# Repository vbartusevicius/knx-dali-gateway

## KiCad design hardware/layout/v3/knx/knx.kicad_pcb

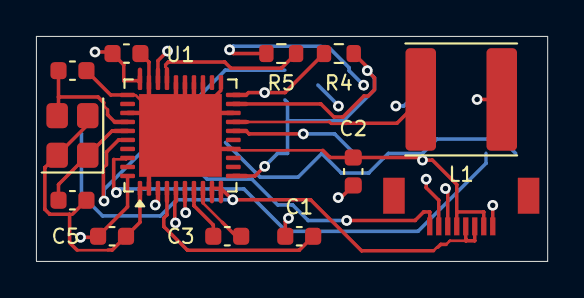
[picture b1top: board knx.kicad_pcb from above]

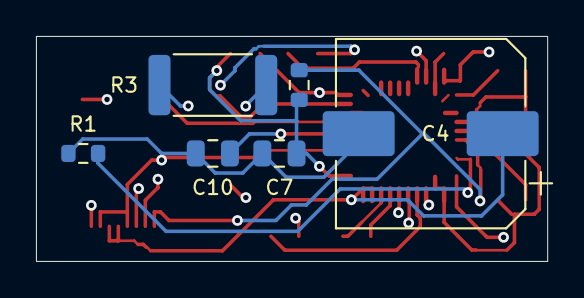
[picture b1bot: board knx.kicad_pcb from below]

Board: 4 copper layers, 28.4 x 12.5 mm, 19 parts (6 on the bottom side), 18 nets.

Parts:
C1: 47n 50V; C_0603_1608Metric
C2, C5, C6: 100n 50V; C_0603_1608Metric
C3: 220n 50V; C_0603_1608Metric
C4: 470u 35V; CP_Elec_10x10
C7: 22u 25V; C_0805_2012Metric
C8, C9: 18p C0G 50V; C_0603_1608Metric
C10: 1u 50V; C_0805_2012Metric
J1: Carrier; FPC_Kinghelm_KH-FPC0.5-H1.2SMT-8P
L1: 220uH; L_Sunlord_SWPA6045S
R1: 10k 1%; R_0603_1608Metric
R2: 10k; R_0603_1608Metric
R3: 27R; R_2512_6332Metric
R4: 1R; R_0603_1608Metric
R5: 1k; R_0603_1608Metric
U1: NCN5130MNTWG; QFN-40-1EP_6x6mm_P0.5mm_EP4.6x4.6mm
Y1: 16MHz; Crystal_SMD_3225-4Pin_3.2x2.5mm

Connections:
+3V3_TRX: C5.1, C6.1, C7.1, R2.1, R4.2, U1.11, U1.19, U1.30, U1.40
CAV: C2.1, U1.5
CCP: C1.2, U1.4
CEQ1: C3.1, U1.7
CEQ2: C3.2, U1.8
FANIN: R1.1, U1.38
GND: C2.2, C4.2, C5.2, C6.2, C7.2, C8.2, C9.2, C10.2, J1.2, J1.5, R1.2, U1.1, U1.2, U1.14, U1.18, U1.21, U1.23, U1.24, U1.25, U1.26, U1.29, U1.31, U1.33, U1.41, Y1.2, Y1.4
KNX_P_PROT: C1.1, J1.1, R3.1, U1.6
KNX_RXD: J1.7, R5.1
KNX_TXD: J1.6, U1.28
unnamed: R5.2, U1.27
NCN_SAVEB: J1.8, R2.2, U1.36
TX0: R3.2, U1.3
VDD1M: L1.2, R4.1, U1.20
VFILT: C4.1, C10.1, J1.3, J1.4, U1.9, U1.10, U1.16
VSW1: L1.1, U1.17
XTAL1: C8.1, U1.35, Y1.1
XTAL2: C9.1, U1.34, Y1.3

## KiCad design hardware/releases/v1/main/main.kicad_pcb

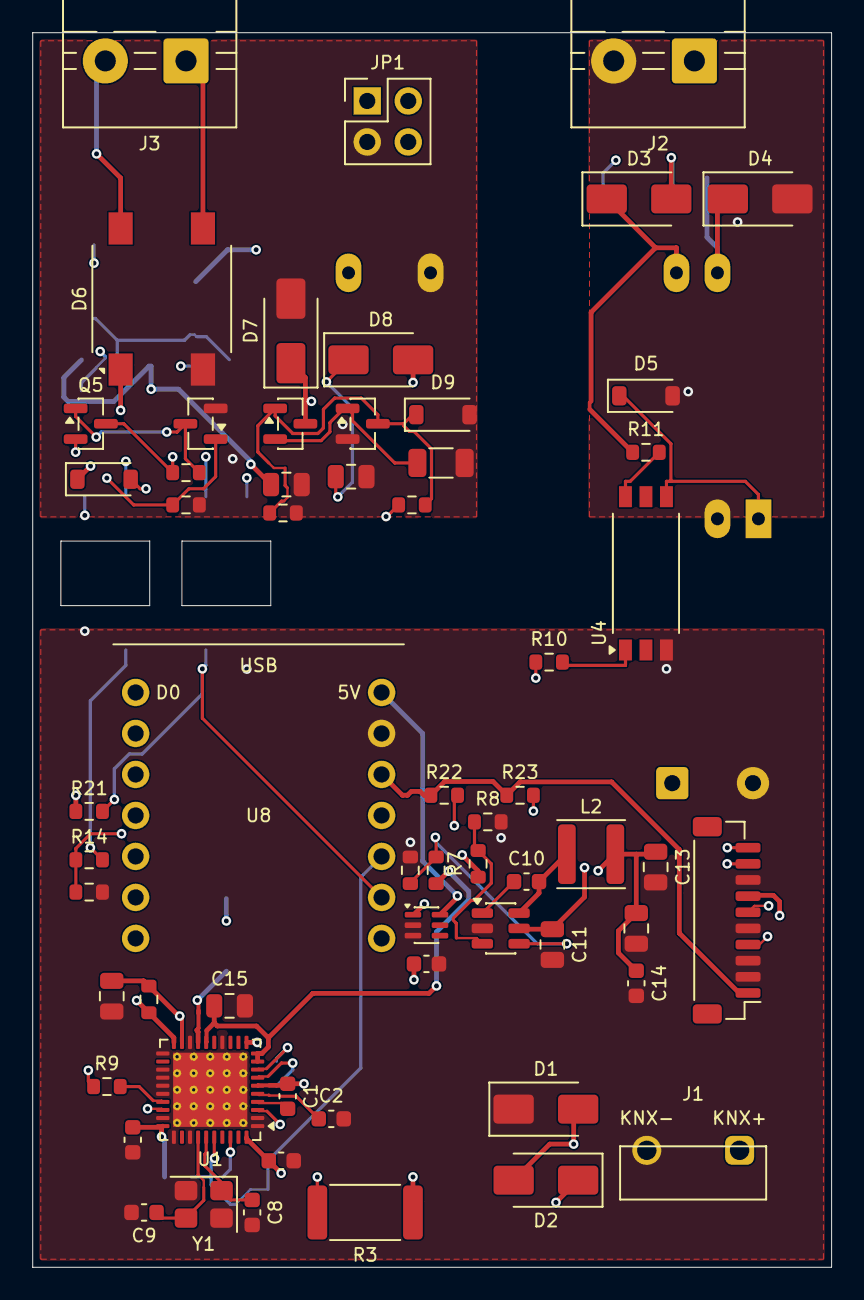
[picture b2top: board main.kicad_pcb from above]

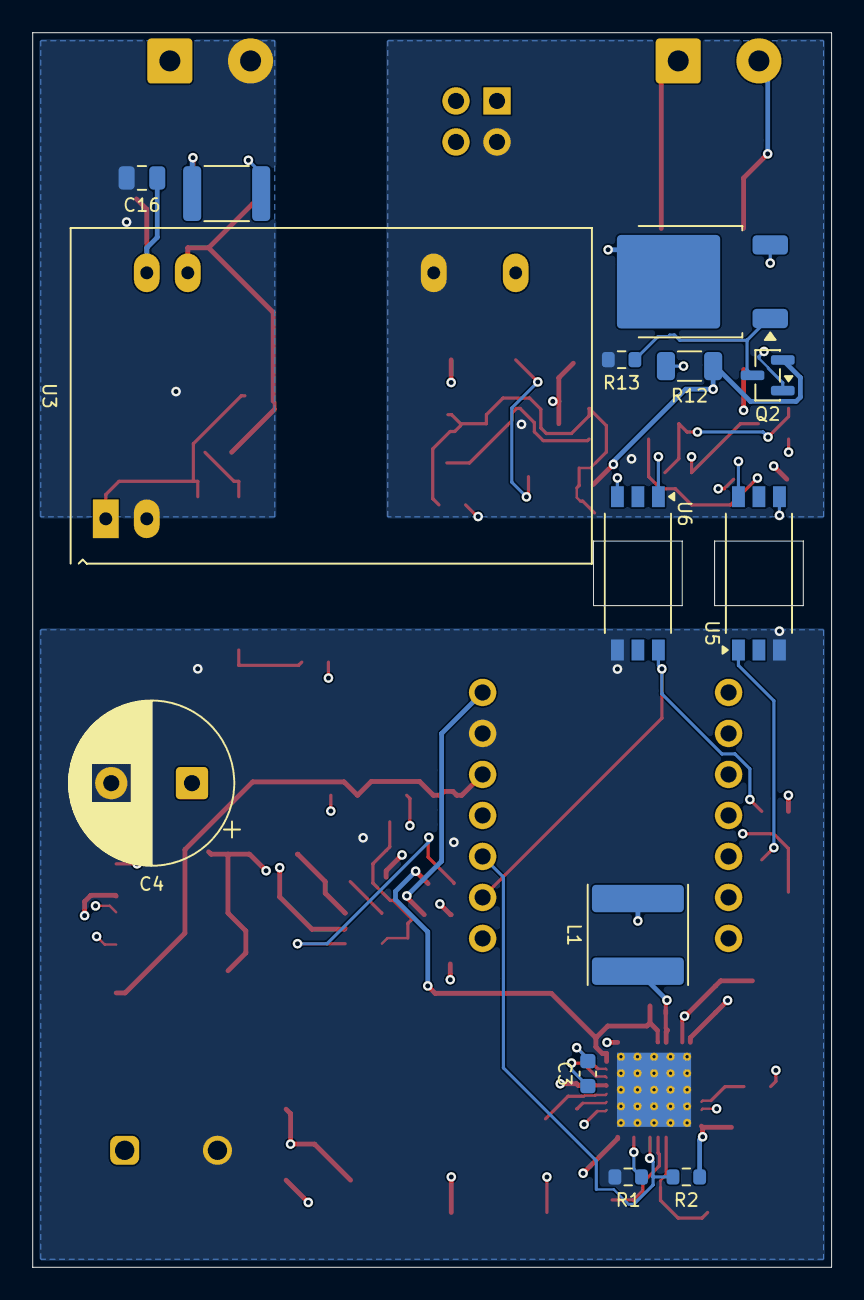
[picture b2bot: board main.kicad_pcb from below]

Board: 4 copper layers, 49.5 x 76.5 mm, 75 parts (14 on the bottom side), 57 nets.

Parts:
C1: 47n 50V; C_0603_1608Metric
C2, C5, C6, C10, C14: 100n 50V; C_0603_1608Metric
C3: 220n 50V; C_0603_1608Metric
C4: 470u 35V; CP_Radial_D10.0mm_P5.00mm
C7, C12, C13: 22u 25V; C_0805_2012Metric
C8, C9: 18p C0G 50V; C_0603_1608Metric
C11, C16: 10u 50V; C_0805_2012Metric
C15, C18: 1u 50V; C_0805_2012Metric
C17: 10u 25V; C_0805_2012Metric
C19: 10u 10V; C_0603_1608Metric
D1: SMAJ40CA; D_SMA
D2, D3, D8: SS16; D_SMA
D4: SMAJ33A; D_SMA
D5, D10: 5V6; D_SOD-123
D6: DF06S; Diode_Bridge_Vishay_DFS
D7: SMAJ24A; D_SMA
D9: 12V; D_SOD-123
F1: 1.1A; Fuse_1812_4532Metric
J1: KNX bus terminal pins; Phoenix_PST_1,0-2-5,75_R32_1x02_P5.75mm
J2: AUX; TerminalBlock_MaiXu_MX126-5.0-02P_1x02_P5.00mm
J3: DALI; TerminalBlock_MaiXu_MX126-5.0-02P_1x02_P5.00mm
J4: JST-SH 1x10; JST_SH_BM10B-SRSS-TB_1x10-1MP_P1.00mm_Vertical
JP1: DALI supply; PinHeader_2x02_P2.54mm_Vertical
L1: 220uH; L_Sunlord_SWPA6045S
L2: 4.7uH; L_APV_ANR4012
Q1: MJD45H11; TO-252-2
Q2: BC857; SOT-23
Q3: IRLML0060; SOT-23
Q4, Q5, Q6: BC847; SOT-23
R1, R6, R8: 10k 1%; R_0603_1608Metric
R2, R11, R15, R21: 10k; R_0603_1608Metric
R3: 27R; R_2512_6332Metric
R4: 1R; R_0603_1608Metric
R5: 120k 1%; R_0603_1608Metric
R7: 51k 1%; R_0603_1608Metric
R9: 1k; R_0603_1608Metric
R10, R14: 330R; R_0603_1608Metric
R12, R18: 3R3; R_1206_3216Metric
R13, R22, R23: 4k7; R_0603_1608Metric
R16: 22k; R_0603_1608Metric
R17, R19: 100k; R_0603_1608Metric
R20: 680R; R_0603_1608Metric
U1: NCN5130MNTWG; QFN-40-1EP_6x6mm_P0.5mm_EP4.6x4.6mm_ThermalVias
U2: SCT2400TVBR; TSOT-23-6
U3: REC3-2415SRW/H2/A/CTRL 24V->15V 3W iso; Converter_DCDC_RECOM_REM3_DIP24_CTRL
U4: TLP383; SO-6L_10x3.84mm_P1.27mm
U5, U6: TLP383(D4BLLTL,E; SO-6L_10x3.84mm_P1.27mm
U7: LM66100; SOT-363_SC-70-6
U8: XIAO ESP32C6; XIAO_ESP32C6_Header
Y1: 16MHz; Crystal_SMD_3225-4Pin_3.2x2.5mm

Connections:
+3V3: J4.1, R21.1, R22.1, R23.1, U8.12
+3V3_TRX: C5.1, C6.1, C7.1, R2.1, R4.2, U1.11, U1.19, U1.30, U1.40
+5V: C12.1, C13.1, C14.1, J4.7, L2.2, R7.1, U7.1
+5V_XIAO: C19.1, U7.6, U8.14
AUX_FUSED: D3.2, F1.2
AUX_P: C16.1, D3.1, D4.1, R11.1, U3.22, U3.23
BTN_LADDER: J4.4, U8.3
CAV: C2.1, U1.5
CCP: C1.2, U1.4
CEQ1: C3.1, U1.7
CEQ2: C3.2, U1.8
DA1: D6.3, J3.1, JP1.2
DA2: D6.4, J3.2, JP1.4
DALI_BOOT: C18.1, D8.1, U5.6
DALI_GATE: D9.1, Q3.1, Q4.3, R16.2, R17.1
DALI_GATE_SW: R16.1, U5.4
DALI_ISO15V: C17.1, Q2.2, R12.1, U3.14
DALI_RX: R21.2, U6.6, U8.9
DALI_SENSE: Q3.2, Q4.1, R18.1
DALI_SUPPLY_OFF: R10.1, U8.2
DALI_SUPPLY_SW: JP1.1, Q1.2
DALI_TX: R14.1, R15.1, U8.11
DA_P: D6.1, D7.1, D8.2, D10.1, Q3.3
FANIN: R1.1, U1.38
GND: C2.2, C4.2, C5.2, C6.2, C7.2, C8.2, C9.2, C11.2, C12.2, C13.2, C14.2, C15.2, C19.2, D1.1, J1.2, J4.2, J4.3, J4.5, J4.8, R1.2, R6.2, R8.2, R15.2, U1.1, U1.2, U1.14, U1.18, U1.21, U1.23, U1.24, U1.25, U1.26, U1.29, U1.31, U1.33, U1.41, U2.2, U4.3, U5.3, U6.4, U7.2, U7.3, U8.13, Y1.2, Y1.4
GNDA: C16.2, D4.2, D5.2, J2.2, U3.2
GNDD: C17.2, C18.2, D6.2, D7.2, D9.2, JP1.3, Q4.2, Q6.2, R13.2, R17.2, R18.2, R20.2, U3.16
I2C_SCL: J4.10, R23.2, U8.6
I2C_SDA: J4.9, R22.2, U8.5
KNX_P: D1.2, D2.2, J1.1
KNX_P_PROT: C1.1, D2.1, R3.1, U1.6
KNX_RXD: R9.1, U8.7
KNX_TXD: U1.28, U8.8
LED_DATA: J4.6, U8.1
unnamed: R5.2, R6.1, U2.4
unnamed: C10.1, U2.1
unnamed: R7.2, R8.1, U2.3
unnamed: R9.2, U1.27
unnamed: F1.1, J2.1
unnamed: R10.2, U4.1
unnamed: R11.2, U4.6
unnamed: D5.1, U3.1, U4.4
unnamed: Q1.3, Q2.1, R12.2
unnamed: Q1.1, Q2.3, R13.1
unnamed: R14.2, U5.1
unnamed: D10.2, U6.1
unnamed: Q5.2, Q6.1, R20.1
unnamed: Q5.1, Q6.3, R19.2
NCN_SAVEB: R2.2, U1.36, U8.10
RX_LIM_IN: Q5.3, R19.1, U6.3
SW: C10.2, L2.1, U2.6
TX0: R3.2, U1.3
VDD1M: L1.2, R4.1, U1.20
VFILT: C4.1, C11.1, C15.1, R5.1, U1.9, U1.10, U1.16, U2.5
VSW1: L1.1, U1.17
XTAL1: C8.1, U1.35, Y1.1
XTAL2: C9.1, U1.34, Y1.3

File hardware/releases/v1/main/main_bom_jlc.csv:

Comment,Designator,Footprint,LCSC Part #
1.1A,F1,Fuse_1812_4532Metric,C142747
100k,"R17,R19",R_0603_1608Metric,C25803
100n 50V,"C10,C14,C2,C5,C6",C_0603_1608Metric,C14663
10k,"R11,R15,R2,R21",R_0603_1608Metric,C25804
10k 1%,"R1,R6,R8",R_0603_1608Metric,C25804
10u 10V,C19,C_0603_1608Metric,C19702
10u 25V,C17,C_0805_2012Metric,C15850
10u 50V,"C11,C16",C_0805_2012Metric,C440198
120k 1%,R5,R_0603_1608Metric,C25808
12V,D9,D_SOD-123,C72599
16MHz,Y1,Crystal_SMD_3225-4Pin_3.2x2.5mm,C12668
18p C0G 50V,"C8,C9",C_0603_1608Metric,C1647
1R,R4,R_0603_1608Metric,C22936
1k,R9,R_0603_1608Metric,C21190
1u 50V,"C15,C18",C_0805_2012Metric,C28323
220n 50V,C3,C_0603_1608Metric,C64705
220uH,L1,L_Sunlord_SWPA6045S,C91047
22k,R16,R_0603_1608Metric,C31850
22u 25V,"C12,C13,C7",C_0805_2012Metric,C45783
27R,R3,R_2512_6332Metric,C25478
330R,"R10,R14",R_0603_1608Metric,C23138
3R3,"R12,R18",R_1206_3216Metric,C17945
4.7uH,L2,L_APV_ANR4012,C135248
470u 35V,C4,CP_Radial_D10.0mm_P5.00mm,C165500
47n 50V,C1,C_0603_1608Metric,C1622
4k7,"R13,R22,R23",R_0603_1608Metric,C23162
51k 1%,R7,R_0603_1608Metric,C23196
5V6,"D10,D5",D_SOD-123,C236111
680R,R20,R_0603_1608Metric,C23228
AUX,J2,TerminalBlock_MaiXu_MX126-5.0-02P_1x02_P5.00mm,C5188434
BC847,"Q4,Q5,Q6",SOT-23,C57668
BC857,Q2,SOT-23,C181147
DALI,J3,TerminalBlock_MaiXu_MX126-5.0-02P_1x02_P5.00mm,C5188434
DALI supply,JP1,PinHeader_2x02_P2.54mm_Vertical,C66690
DF06S,D6,Diode_Bridge_Vishay_DFS,C460867
IRLML0060,Q3,SOT-23,C67274
JST-SH 1x10,J4,JST_SH_BM10B-SRSS-TB_1x10-1MP_P1.00mm_Vertical,C160396
LM66100,U7,SOT-363_SC-70-6,C2869734
MJD45H11,Q1,TO-252-2,C48580717
NCN5130MNTWG,U1,QFN-40-1EP_6x6mm_P0.5mm_EP4.6x4.6mm_ThermalVias,C513000
SCT2400TVBR,U2,TSOT-23-6,C2693819
SMAJ24A,D7,D_SMA,C148222
SMAJ33A,D4,D_SMA,C113966
SMAJ40CA,D1,D_SMA,C113970
SS16,"D2,D3,D8",D_SMA,C2481
TLP383,U4,SO-6L_10x3.84mm_P1.27mm,C3002263
"TLP383(D4BLLTL,E","U5,U6",SO-6L_10x3.84mm_P1.27mm,C3002263

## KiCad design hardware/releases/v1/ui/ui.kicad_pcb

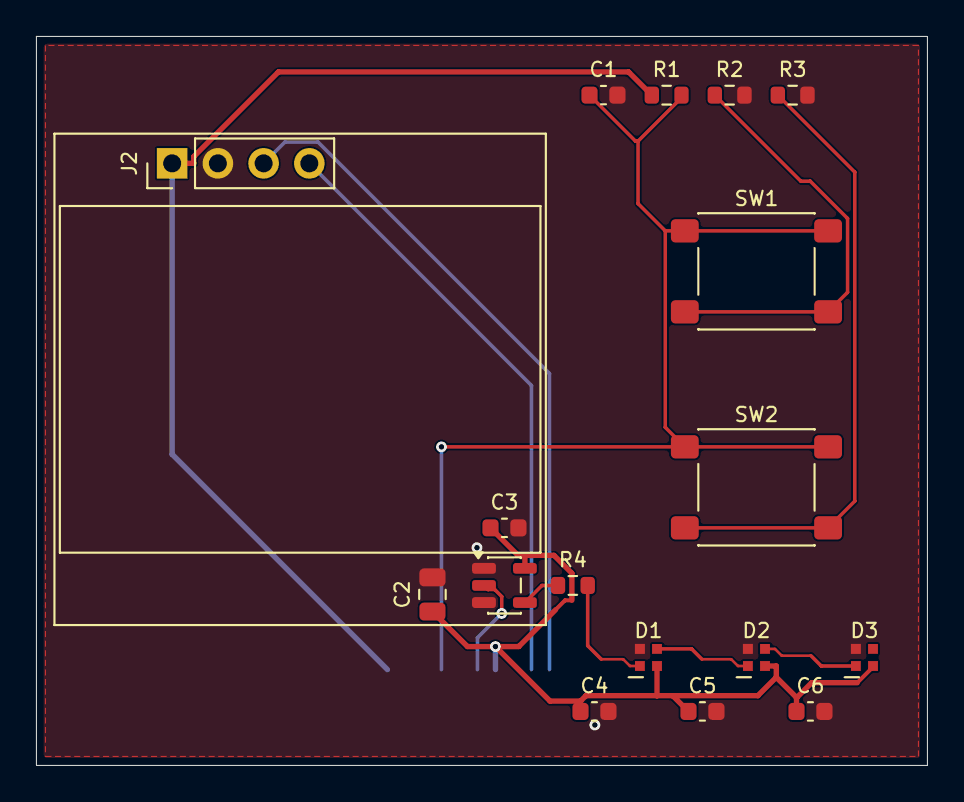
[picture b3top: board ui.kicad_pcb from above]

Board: 2 copper layers, 49.5 x 40.5 mm, 18 parts (1 on the bottom side), 13 nets.

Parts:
C1, C3, C4, C5, C6: 100n 50V; C_0603_1608Metric
C2: 1u 50V; C_0805_2012Metric
D1: RGB STATUS; LED_SK6805-EC15_1.5x1.5mm
D2: RGB KNX; LED_SK6805-EC15_1.5x1.5mm
D3: RGB DALI; LED_SK6805-EC15_1.5x1.5mm
J1: JST-SH 1x10; JST_SH_BM10B-SRSS-TB_1x10-1MP_P1.00mm_Vertical
J2: OLED; PinHeader_1x04_P2.54mm_Vertical
R1, R3: 10k; R_0603_1608Metric
R2: 20k; R_0603_1608Metric
R4: 330R; R_0603_1608Metric
SW1: PRG/RST; SW_SPST_PTS645Sx43SMTR92
SW2: FUNC; SW_SPST_PTS645Sx43SMTR92
U1: 74AHCT1G125; SOT-23-5

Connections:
+3V3: J1.1, J2.1, R1.1
+5V: C2.1, C3.1, C4.1, C5.1, C6.1, D1.2, D2.2, D3.2, J1.7, U1.5
BTN_LADDER: C1.1, J1.4, R1.2, SW1.1, SW2.1
GND: C1.2, C2.2, C3.2, C4.2, C5.2, C6.2, D1.4, D2.4, D3.4, J1.2, J1.3, J1.5, J1.8, J2.2, R2.2, R3.2, U1.1, U1.3
I2C_SCL: J1.10, J2.3
I2C_SDA: J1.9, J2.4
LED_CHAIN1: D1.3, D2.1
LED_CHAIN2: D2.3, D3.1
LED_DATA: J1.6, U1.2
unnamed: R2.1, SW1.2
unnamed: R3.1, SW2.2
unnamed: R4.1, U1.4
unnamed: D1.1, R4.2

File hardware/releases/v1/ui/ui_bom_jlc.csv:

Comment,Designator,Footprint,LCSC Part #
100n 50V,"C1,C3,C4,C5,C6",C_0603_1608Metric,C14663
10k,"R1,R3",R_0603_1608Metric,C25804
1u 50V,C2,C_0805_2012Metric,C28323
20k,R2,R_0603_1608Metric,C4184
330R,R4,R_0603_1608Metric,C23138
74AHCT1G125,U1,SOT-23-5,C7484
FUNC,SW2,SW_SPST_PTS645Sx43SMTR92,C285485
JST-SH 1x10,J1,JST_SH_BM10B-SRSS-TB_1x10-1MP_P1.00mm_Vertical,C160396
PRG/RST,SW1,SW_SPST_PTS645Sx43SMTR92,C285485
RGB DALI,D3,LED_SK6805-EC15_1.5x1.5mm,C2890035
RGB KNX,D2,LED_SK6805-EC15_1.5x1.5mm,C2890035
RGB STATUS,D1,LED_SK6805-EC15_1.5x1.5mm,C2890035
